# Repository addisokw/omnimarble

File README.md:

# OmniMarble -- Magnetic Coil Marble Coaster Digital Twin

A physics-accurate digital twin of a magnetic coil-launched marble roller coaster, built on NVIDIA's simulation stack (OpenUSD, PhysX, Kit SDK) with a Physics-Informed Neural Network (PINN) for real-time electromagnetic field computation.

## How It Works

A solenoid coil fires an RLC capacitor discharge through a coil to accelerate a ferromagnetic marble via electromagnetic force. The complete physics chain:

```
RLC Circuit (V, C, L, R)
    |
    v
Current I(t) -- underdamped oscillation with flyback diode
    |
    v
B-field (PINN: 6 inputs -> Br, Bz in single forward pass)
    |
    v
Gradient dB/dr, dB/dz (torch.autograd on PINN output)
    |
    v
Force F = (chi*V/mu0) * (B . nabla)B  -- with saturation + eddy braking
    |
    v
PhysX apply_force_at_pos() -- marble accelerates in Omniverse
```

### The PINN

The analytical Biot-Savart computation (30 loop iterations x scipy elliptic integrals) is replaced by a Physics-Informed Neural Network for real-time inference:

- **Architecture (v8, "physics by construction")**: NVIDIA PhysicsNeMo FullyConnected, 6x256 hidden, SiLU, skip connections. The network outputs a single scalar f; the vector potential is A_phi = r*f and the field is derived inside forward() via autograd: B_r = -r*df/dz, B_z = 2f + r*df/dr. This makes div(B)=0, curl consistency, and the on-axis boundary conditions **exact identities of the architecture**, not trained approximations.
- **Inputs**: (r, z, I, N, R_mean, L) -- spatial position + coil design parameters
- **Outputs**: (A_phi, B_r, B_z) -- same column contract as earlier direct-B models; the shared loader (`scripts/pinn_loader.py`) handles both generations via the checkpoint's `derived_b` flag
- **Key feature**: Model learns B/I (T/A), collapsing dynamic range across the full current range [0.5, 4000] A
- **Training**: 1.42M samples from analytical Biot-Savart (711 configs incl. failure-mined families), losses: data + far-field decay + z-mirror symmetry
- **Validation**: 5-level test suite -- field accuracy, gradient accuracy, force accuracy, design space coverage, physics consistency
- **Force**: needs field gradients, which are second derivatives of f (double backward through the forward-pass graph)

### RLC Circuit

The coil is driven by a capacitor discharge (underdamped RLC):

```
I(t) = (V0 / omega_d * L) * exp(-alpha * t) * sin(omega_d * t)
```

With coupled electromechanical ODE (back-EMF from marble motion), RK4 sub-stepping at 10us resolution, and flyback diode clamping.

Default circuit: 470uF capacitor, 50V charge, L=12.4uH, R_dc=0.080 ohm (config `resistance_ohm`) + 0.01 ESR + 0.02 wiring = R_total~=0.110 ohm -> underdamped (zeta=0.34). Peak current: 327A undamped amplitude V/(omega_d*L); ~198A true damped peak (the two pipelines historically reported different definitions -- see tests/test_coil_physics.py).

### Force Model

Force on a ferromagnetic sphere in a non-uniform field:

```
F = (chi_eff * V / mu0) * (B . nabla)B
```

Where:
- chi_eff = 3.0 (demagnetization-corrected susceptibility for a sphere)
- V = marble volume (mm^3)
- mu0 = 4*pi*1e-4 T*mm/A (mm-scaled)
- B and gradients from PINN autograd

Additional physics:
- **Saturation**: When B_internal > B_sat (1.8T), switches to saturated magnetization model
- **Eddy current braking**: F_eddy proportional to dB/dt and marble conductivity
- **Wire heating**: I^2*R thermal model with copper temperature coefficient

### Units

All computations use mm-based units:
- Distance: mm
- Current: A
- Field: T (Tesla)
- Force: mN (milliNewtons) -- because `[chi * mm^3 / (T*mm/A)] * T * T/mm = A*T*mm = mN`
- Mass: kg (PhysX requirement)
- mu0 = 4*pi*1e-4 T*mm/A

## Quick Start

### Prerequisites

- Python 3.12 or 3.13 — **not 3.14**, which has no `usd-core` wheels. If your
  system Python is newer, pin the project with `uv python pin 3.13` (uv
  downloads a managed interpreter; `.python-version` is gitignored).
- [uv](https://docs.astral.sh/uv/) package manager
- NVIDIA GPU (CUDA) for PINN training and inference
- [NVIDIA Kit SDK](https://github.com/NVIDIA-Omniverse/kit-app-template) for the Omniverse app

### 1. Install Dependencies

```bash
uv sync
```

This installs torch (CUDA 12.8), nvidia-physicsnemo, scipy, matplotlib, numpy, and other dependencies from `pyproject.toml`.

Verify the GPU is actually usable — a Blackwell card (RTX 50-series) needs
`sm_120` in torch's arch list, which the pinned cu128 build provides:

```bash
uv run python -c "import torch; print(torch.__version__, torch.cuda.get_arch_list())"
```

### 2. Train the PINN (or use existing checkpoint)

A trained checkpoint is included at `models/pinn_checkpoint/pinn_best.pt`
(v8 step-250k, `derived_b=True`). To retrain:

```bash
# Generate training data from analytical Biot-Savart (~1.42M samples)
uv run python scripts/generate_training_data.py

# Train v8 PINN (300k steps, ~4.7h on RTX 5090 — the data loss backprops
# through an autograd derivative, so every step is a double backward)
uv run python scripts/train_pinn.py
# Smoke test without touching the production checkpoint:
uv run python scripts/train_pinn.py --steps 500 --batch-size 16384 --out-name pinn_smoke
```

For remote GPU training (e.g., a more powerful machine on your network):
```bash
# Edit REMOTE_HOST and REMOTE_USER in the script, then:
bash scripts/remote_train.sh
# Pulls the result as pinn_v8_candidate.pt + step checkpoints to
# candidates/v8/ — promotion to pinn_best.pt is a manual decision after
# the adoption-gate evaluation (see below).
```

### 3. Validate the PINN

```bash
uv run python scripts/evaluate_pinn.py            # validates pinn_best.pt
uv run python scripts/evaluate_pinn.py --ckpt <path>   # validate a candidate
```

Runs a 5-level validation suite:
1. **Field accuracy**: Bz error vs analytical at 6 currents (12,800 points each)
2. **Gradient accuracy**: dB/dr, dB/dz via autograd vs finite-difference
3. **Force accuracy**: End-to-end F_z comparison at r=0 and r=5mm
4. **Design space**: 64 coil geometries (N x R_mean x L grid)
5. **Physics consistency**: div(B)=0, axial symmetry, z-mirror symmetry

Outputs:
- Console: PASS/FAIL per check
- Plots: `results/plots/pinn_validation/` (5 figures)
- JSON: `results/pinn_validation_report.json`
- Audit: `results/pinn_audit_report.md`

### 4. Analytical B-Field Validation

```bash
uv run python scripts/analytical_bfield.py
```

Generates reference plots in `results/plots/`.

### 5. Coil Design Optimizer

#### Web UI (Gradio)

```bash
uv run python scripts/coil_optimizer_app.py
```

Opens a browser UI for interactive multi-objective coil design optimization.
Features: constraint sliders, target-boost mode, Pareto plot, coupled ODE reranking.

#### CLI

```bash
uv run python scripts/optimize_coil_design.py
```

Headless optimization — prints top designs to console with Pareto plot saved to `results/`.

### 6. Run in NVIDIA Kit (Omniverse)

#### First-time setup

The Kit SDK is not vendored. `omnimarble.kit.bat` expects a
`kit-app-template` checkout **as a sibling of this repo**, with our app and
extension registered inside it. None of that wiring is tracked in git, so it
has to be redone on each new machine.

Verified against kit-app-template **110.2.0**. Windows needs no Visual Studio
— that template disables the C++ build step on `windows-x86_64`.

```cmd
REM 1. Clone kit-app-template next to this project
git clone https://github.com/NVIDIA-Omniverse/kit-app-template.git ..\kit-app-template

REM 2. A fresh clone has no source/ tree at all -- create it.
mkdir ..\kit-app-template\source\apps
mkdir ..\kit-app-template\source\extensions

REM 3. Register the app. Template 110.x expects a FLAT .kit file in
REM    source/apps -- not the nested apps/<name>/<name>.kit of older releases.
copy source\apps\omnimarble\omnimarble.kit ..\kit-app-template\source\apps\

REM 4. Link the extension back here so it stays live-editable. Path.resolve()
REM    follows the junction, so the extension's config/coil_params.json
REM    ancestor-walk still finds this project root.
mklink /J ..\kit-app-template\source\extensions\omni.marble.coaster ^
          source\extensions\omni.marble.coaster
```

Then register the app in the two build files in `../kit-app-template`.
Extensions are auto-discovered from the directory layout, so only the app
needs declaring:

```lua
-- premake5.lua -- append after the "Apps:" comment at the end
define_app("omnimarble.kit")
```

```toml
# repo.toml -- the section already exists with an empty list; fill it in
[repo_precache_exts]
apps = [
    "${root}/source/apps/omnimarble.kit",
]
```

Finally build (downloads ~10GB, one-time):

```cmd
cd ..\kit-app-template
.\repo.bat build
cd ..\omnimarble
```

#### Launch

```cmd
omnimarble.kit.bat
```

This launches Kit with the extension loaded directly from `source/extensions/` (live editing).

**First launch is slow.** The extension pip-installs its own torch into Kit's
embedded Python (3.12) at
`%LOCALAPPDATA%\ov\data\Kit\omnimarble\1.0\pip3-envs\default-3.12` — a
separate environment from this project's `.venv`. Both `torch` and
`torchvision` are pinned to `+cu128` builds in `extension.py`
(`TORCH_CUDA_VERSION` / `TORCHVISION_CUDA_VERSION`); without the pins pip
prefers PyPI's CPU-only Windows wheel and the PINN runs ~13x slower with no
other symptom. A healthy startup logs:

```
[PINN] torch 2.10.0+cu128 (CUDA 12.8), physicsnemo ready
[PINN] Loaded on cuda, checkpoint: ...\pinn_best.pt
```

If it says `CUDA None` or `Loaded on cpu`, a stale wheel is cached:
`omni.kit.pipapi.install` skips whenever the module already imports, so
delete `torch*` from that `pip3-envs` directory and relaunch. Note that
`torchvision` must go back too — `physicsnemo` imports `timm`, which imports
`torchvision`, and its absence surfaces misleadingly as *"Checkpoint was
trained with physicsnemo backend but nvidia-physicsnemo is not installed"*.

#### In the Kit app

1. Click **Load Scene** to open the USD marble coaster scene
2. Click **Configure PhysX** to set CCD, 500Hz timestep, damping
3. Click **Start Simulation** -- marble rolls down the track, triggers IR gates, fires the coil
4. Watch the console log for real-time telemetry (current, field, force, velocity)
5. Adjust **Charge Voltage** and **Capacitance** in the UI panel, click **Update Parameters**
6. Click **Stop Simulation** -- the run's trajectory is written to
   `results/trajectories/kit_launch_<V>V_<C>uF_<timestamp>.csv`

#### Scripted autorun (reproducible launch runs)

The full sequence (load scene, configure PhysX, voltage override, start,
stop after the exit gates fire, write CSV, quit) can be driven without
clicking:

```cmd
omnimarble.kit.bat --/exts/omni.marble.coaster/autorun=true --/exts/omni.marble.coaster/autorunVoltage=300
```

Optional: `autorunMaxSimSeconds` (default 12), `autorunKeepOpen=true` to
leave the app running after the CSV is written.

#### Trajectory export

Every physics step records time, position (world + coil-local z_along/r),
velocities, coil current, capacitor voltage, PINN force and Bz, wire
temperature, and trigger/cutoff flags. The CSV starts with `# key=value`
metadata lines (run parameters, PINN checkpoint + step, gate times,
approach/exit velocity, boost ratio).

A committed reference artifact from the real Kit/PhysX/PINN path:
`results/trajectories/kit_launch_300V_470uF_20260702_174018.csv` — 300V run,
approach 208 mm/s, gate-measured exit 937.5 mm/s (**4.5x boost**).

Use it to check a fresh machine: rerun the autorun command above and diff.
The gate-measured numbers and the `current_A` / `V_cap_V` / `Bz_T` /
`wire_temp_C` columns should match exactly. Positions and velocities drift
slightly (sub-0.1mm, well under 1% on velocity) — that is PhysX solver
nondeterminism across machines, not a broken setup.

#### What happens during simulation

1. Marble rolls down the starter slope under gravity
2. Two velocity-measurement IR gates compute approach velocity
3. Entry gate triggers the RLC discharge
4. Coupled electromechanical ODE computes current with 10us sub-stepping
5. PINN computes B-field, autograd computes gradients, force is applied via PhysX
6. Cutoff gate (MOSFET switch) kills the pulse when marble passes coil center
7. Two exit gates measure the launch velocity and compute boost ratio

## Project Structure

```
config/
  coil_params.json              # Source of truth: coil geometry + RLC circuit params

scripts/
  analytical_bfield.py          # Biot-Savart B-field (elliptic integrals) -- ground truth
  generate_training_data.py     # PINN training data from analytical solution (1.42M samples)
  pinn_loader.py                # Shared checkpoint loader + inference (legacy & derived-B)
  train_pinn.py                 # v8 derived-B PINN training (PhysicsNeMo)
  evaluate_pinn.py              # 5-level PINN validation suite (--ckpt for candidates)
  evaluate_candidates.py        # Multi-checkpoint Pareto comparison
  v7_optimization_diagnostic.py # PINN ranking stability diagnostic (--ckpt)
  physical_accuracy_audit.py    # Physics consistency validation
  validate_physics.py           # Physics validation utilities
  validate_kit_simulation.py    # Headless mirror of Kit physics (--field pinn|analytical)
  coil_optimizer_core.py        # Shared optimization engine (screening + coupled reranking)
  coil_optimizer_app.py         # Gradio web UI for coil design optimizer
  optimize_coil_design.py       # CLI coil design optimizer
  warp_bfield_solver.py         # PINN-based solver for headless simulation
  rlc_circuit.py                # RLC circuit utilities (saturation, eddy braking)
  remote_train.sh               # Remote GPU training via SSH
  generate_coil.py              # Parametric coil mesh generation
  em_force_injection.py         # Standalone EM force simulation
  simulation_loop.py            # Full orchestration loop
  optimize_launch.py            # Differentiable parameter optimization
  create_marble.py              # Marble actor creation
  compose_scene.py              # Scene composition from USD layers
  convert_stl_to_usd.py         # STL → USD conversion
  add_visuals.py                # Visual enhancement
  setup_launch_scene.py         # Launch scene setup
  run_physics_test.py           # Physics test runner

source/                         # NVIDIA Kit extension
  apps/omnimarble/
    omnimarble.kit              # Kit app configuration
  extensions/omni.marble.coaster/
    config/extension.toml       # Extension settings (overridable defaults)
    omni/marble/coaster/
      extension.py              # Main extension: RLC + PINN + PhysX force + UI + autorun
      coil_physics.py           # Pure-Python coil/RLC physics (unit-testable, no Kit deps)

tests/                          # pytest suite (uv run pytest)
  test_coil_physics.py          # Derived values vs config, RLC, gates, cross-checks
  test_rlc_circuit.py           # Saturation/eddy/thermal helpers, mm/mN/T unit system
  test_pinn_loader.py           # Loader version detection, derived-B structural guarantees

models/
  pinn_checkpoint/
    pinn_best.pt                # Production checkpoint: v8 step-250k, derived_b=True
                                # (historical v3-v7 checkpoints live in git history;
                                #  candidates/ holds gitignored periodic checkpoints)

usd/                            # USD scene layers
  marble_coaster_scene.usda     # Composed scene (references all layers)
  marble_actor.usda             # Marble rigid body (mass=0.00408kg)
  coil_geometry.usda            # Coil mesh
  coil_properties.usda          # Coil electrical properties
  track_geometry.usda           # Track collision mesh
  marble_trajectory.usda        # Trajectory reference
  physics_config.usda           # PhysX configuration
  visual_config.usda            # Visual settings

results/
  pinn_validation_report.json   # Validation metrics (machine-readable)
  pinn_audit_report.md          # Full PINN audit trail
  plots/                        # Generated validation plots

omnimarble.kit.bat              # Launch Kit from project root
```

## Configuration

All physical parameters live in `config/coil_params.json`:

```json
{
  "inner_radius_mm": 12.0,
  "outer_radius_mm": 18.0,
  "length_mm": 30.0,
  "num_turns": 30,
  "capacitance_uF": 470.0,
  "charge_voltage_V": 50.0,
  "esr_ohm": 0.01,
  "wiring_resistance_ohm": 0.02,
  "has_flyback_diode": true,
  "switch_type": "MOSFET"
}
```

The Kit extension reads this JSON as the primary source of truth. UI fields in Kit override individual values at runtime.

**Physical-build note:** the persisted `inductance_uH`/`resistance_ohm`
derive from a 12mm-former winding assumption, while the field model (and
the PINN trained on it) places the windings at R_mean = 15mm — no single
physical coil satisfies both. Build real coils to the field geometry and
overwrite these two values with LCR-measured ones; see
`hardware/README.md` ("Supported coils" / build sheet) for the full
analysis.

### Getting a stronger launch

The default 50V/470uF circuit stores only 0.59J — at 50V the EM force barely
changes the trajectory versus a plain gravity roll. For a visible launch:
- **300V / 470uF**: 21J stored — **demonstrated in Kit: 4.5x gate-measured
  boost** (artifact: `results/trajectories/kit_launch_300V_470uF_20260702_174018.csv`)
- To improve efficiency, increase coil inductance (more turns, tighter winding) so the discharge period (~5-20ms) matches the marble's transit time through the coil

## PINN Training Details

### Architecture (v8, physics by construction)
- NVIDIA PhysicsNeMo FullyConnected backbone
- 6 inputs: (r, z, I, N, R_mean, L); 1 raw output: scalar f
- A_phi = r*f; B_r = -r*df/dz and B_z = 2f + r*df/dr derived via autograd
  in forward() — div(B)=0, curl consistency, and on-axis BCs are exact
- 6 hidden layers x 256 units, SiLU activation, skip connections
- B/I normalization: model learns B/I (T/A), caller multiplies by I
- Canonical model + loader: `scripts/pinn_loader.py` (`BFieldPINNDerived`)

### Training data
- 1.42M samples from analytical Biot-Savart
- 75k spatial point pool: 30k dense near coil + 20k boundary-enriched + 5k on-axis + 20k far-field
- 711 parameter configs: grid corners + random + failure-mined N=10/R=8 families
- Per-config: 1500 general + 500 config-adaptive boundary points

### Loss function (v8)
- **Data loss**: MSE on derived B_r/I and B_z/I (backprops through the
  autograd derivative — the dominant per-step cost)
- **Far-field decay** (weight 0.1): fields -> 0 far from coil
- **z-mirror symmetry** (weight 0.5): Bz even, Br odd in z
- Progressive ramp: physics weights scale from 0.1x to 1.0x over first 20k steps
- Removed vs v7 (now exact by construction): curl, divergence-free, on-axis
  boundary conditions; gradient supervision dropped (third-order, marginal)
- Checkpoint selection by data loss + periodic saves for a post-hoc sweep

### Current validation status (v8 step-250k, production — 2026-07-02)

| Level | Check | Result |
|-------|-------|--------|
| 1 | Field accuracy (mean/max Bz error) | FAIL max-only (mean 0.86%, max 27.8% at winding singularities; informational) |
| 2 | Gradient accuracy (dBz/dz mean + P99) | PASS (P99 3.05%) |
| 3 | Force accuracy (peak err, correlation, zero-crossing) | PASS (2.7% / 3.0%, r>0.994) |
| 4 | Design space (64 configs under 5%) | PASS (95.3%, worst 7.75%) |
| 5 | Physics consistency (div=0, symmetry) | PASS (div(B)=0 exact by construction) |

Optimizer-ranking diagnostic vs analytical reference: Spearman r=1.000,
Kendall tau=0.992 over 60 candidates — safe for design optimization.

See `results/pinn_audit_report.md` for the full audit trail including all
training iterations (v1-v8) and the adoption-gate decision.

## License

MIT

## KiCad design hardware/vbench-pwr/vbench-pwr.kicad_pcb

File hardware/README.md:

# OmniMarble driver board (60V-class SELV coilgun pulse driver)

Experimental-side electronics for the OmniMarble digital twin: drives a
real coil with the same fire/cutoff logic as the simulation's Kit
extension and emits telemetry in the sim's trajectory-CSV format for
direct sim-to-real comparison.

> ⚠️ **vNext — on hold (2026-07-06).** This integrated driver board is not the
> current path. The launch concept is still unproven, so we stepped back to a
> bench rig built from off-the-shelf modules — see **[`V0_BENCH_RIG.md`](V0_BENCH_RIG.md)**.
> This board is DRC-clean and preserved; revisit once V0 proves the concept out.

**Status: layout final — fully routed, electrically DRC-clean (0 unconnected /
shorts / clearance / parity), all validators green, and the JLCPCB fab/assembly
package generated (`hardware/fab/jlc/`). Externally reviewed.**

- Operating point: bank charged **24.5–55 V** (63 V-rated capacitors,
  hardware OVP trips 59.1–62.0 V worst-case, asserted in
  `scripts/calcs.py`), one shot per several seconds.
- Bank: 5× snap-in positions, 2200 µF/63 V each (baseline 2 populated =
  4400 µF; max 11000 µF).
- Switch: 3× paralleled 150 V TOLL MOSFETs, designed to a **600 A / 2 ms**
  pulse point; MOSFET-cutoff + freewheel topology reproduces the sim's
  circuit model.
- All engineering numbers in `design-calcs.md` are generated and
  margin-asserted by `scripts/calcs.py` — do not hand-edit.

## Supported coils

The coil is off-board (J5 barrier terminals) and interchangeable. A coil
is **validated** iff it satisfies the envelope swept by `calcs.py` at the
worst configuration (11000 µF bank at 55 V):

> **L ≥ 1 µH AND R_total ≥ 90 mΩ** (total series resistance *including*
> leads and lugs — keep leads short and heavy)

Below the envelope the pulse can exceed the 600 A switch design point —
do not fire. The envelope numbers live in `coil-envelope.json` (generated
by calcs.py) and are printed on the flyback schematic sheet next to J5;
the full safe/unsafe sweep table is in `design-calcs.md`.

### Validated default: demo coil (the coil the simulation models)

| Parameter | Value |
|---|---|
| Turns / wire | 30 × 0.8 mm (AWG20), single layer |
| Geometry | inner r 12 mm, outer r 18 mm, length 30 mm |
| Inductance | 12.406 µH |
| R_dc / R_total | 80.2 mΩ / **110.2 mΩ** (incl. 30 mΩ ESR+wiring budget) |
| At 55 V / 11000 µF | ~420 A peak, ~1.1 ms, 16.6 J |

Using this coil keeps hardware runs directly comparable to Kit runs
(`config/coil_params.json` is the shared source of truth).

### KNOWN MODEL INCONSISTENCY (affects how you build the coil)

The simulation is internally inconsistent about where the windings sit:

- The **field model** (`analytical_bfield.solenoid_field`, which the PINN
  was trained on and the launch force derives from) places all 30 turns
  at a **single 15.0 mm radius** — the mean of config's inner 12 / outer
  18 mm.
- The **circuit model** (Wheeler inductance + winding resistance in
  `coil_physics.py` / `rlc_circuit.py`) assumes a single layer of 0.8 mm
  wire on a 12 mm former (wire centers ~12.4 mm), which is where config's
  persisted `inductance_uH = 12.406` and `resistance_ohm = 0.0802` come
  from.

No physical coil satisfies both. **Resolution: build to the FIELD
geometry** (that is what the PINN/force model is being validated
against), then reconcile the circuit side by measurement — the config
accepts measured `inductance_uH` / `resistance_ohm` and the RLC model
uses whatever is there. Building at 12 mm instead would bias the field
test: closer windings give a measurably stronger on-axis field than the
model predicts.

### Coil build sheet — experiment #1 (demo coil, field-geometry build)

The field model uses **ideal loop centers**: 30 loops at radius 15.0 mm
with centers at `np.linspace(-15, +15, 30)`. The physical winding must
match **turn centers**, not wire edges. Machine-readable spec:
`hardware/scripts/parts.py DEMO_COIL_BUILD`, contract-tested against the
field model by `tests/test_coil_physics.py::
test_demo_coil_build_matches_field_model` (fails if either side drifts).

| Item | Spec |
|---|---|
| Target geometry | **Wire CENTER radius = 15.0 mm** (this is the spec; former OD follows from your wire) |
| Former | For 0.87 mm finished wire OD (0.8 mm copper + 2×0.035 mm enamel): **~29.13 mm OD**. Measure your wire's finished OD and set former OD = 2×(15.0 − OD/2). 32 mm winding window between flanges |
| Wire | 0.8 mm copper (AWG20) enameled magnet wire, ~3 m incl. leads |
| Turns | **30 turns, single layer, one direction** |
| Spacing | **30 turn CENTERS evenly spanning 30.0 mm** → center-to-center pitch **30/29 ≈ 1.034 mm** (not 1.000). First and last turn centers sit at ±15.0 mm from coil center. NOT close-wound (that compresses the span to ~26 mm and shifts the field profile) |
| Leads | Short and heavy (>=AWG16 or doubled), crimped ring lugs to J5 |

Winding tips: score/print **1.034 mm-pitch** guide grooves (or a printed
thread) so the groove *centers* span exactly 30.0 mm; secure the ends
(CA glue) before the winding relaxes; leave 100 mm tails.

**Verify after winding** (LCR meter ~1 kHz + milliohm measurement), then
**write the measured values into `config/coil_params.json`** so sim and
hardware run identical circuit numbers:

| Quantity | Expected (field-geometry build) | Config's current value |
|---|---|---|
| Inductance | **~17.3 uH** (Wheeler at 15 mm) | 12.406 uH (12.4 mm assumption) |
| R_dc | **~97 mOhm** (2.83 m of AWG20) | 80.2 mOhm |
| R_total w/ leads | ~125–130 mOhm | 110.2 mOhm |
| Envelope check | 127 mOhm >= 90 mOhm, 17 uH >= 1 uH — inside; worst-case pulse ~430 A vs the 600 A design point | — |

### Experiment #2 (after #1 validates the model)

Wind the optimizer-recommended coil below; its predicted **+1.0 m/s
boost is itself a falsifiable prediction** of the digital twin.

### Optimizer-recommended coil for THIS board (55 V / 600 A constrained)

`uv run python scripts/optimize_coil_design.py --max-voltage 55 --max-current 600`
(PINN + coupled-ODE screening, 2000 LHS candidates, run 2026-07-03):

| Parameter | Value |
|---|---|
| Turns / wire | **75 × AWG18 (1.024 mm), 3 layers** |
| Geometry | inner r 8.5 mm, outer r 11.8 mm, length 30.5 mm |
| Inductance / R | 49.4 µH / R_dc 99 mΩ → R_total ~129 mΩ |
| Drive point | ~51 V, ~3700 µF (2 bank cans ≈ 4400 µF is the closest fit) |
| Pulse | 228 A peak, 1.6 ms, 4.8 J, ΔT ≈ 0.3 °C |
| Predicted boost | **+1.0 m/s (0.5 → 1.5 m/s, ~3×)** |

Envelope check: 129 mΩ ≥ 90 mΩ and 49.4 µH ≥ 1 µH — inside. Note the
earlier optimizer result quoted in the repo (396 V / 247 J design) was
computed for an unconstrained rig and is **not** a recommendation for
this board.

Caveat: these predictions come from the PINN + analytical circuit model.
Validating them against reality is this board's entire purpose — treat
the boost figure as a hypothesis, not a spec.

## Safety summary (details in design-calcs.md)

- Hardware interlock: FIRE = MCU_FIRE AND ARM-keyswitch (74LVC1G08), and
  the gate drivers are only powered through the E-STOP (NC) + keyswitch
  loop. Explicit pulldowns on all fire nets.
- Boost charging is fail-safe inhibited: a dead/absent Pico cannot charge.
- Hardware OVP (CJ431 ±0.5 %) independent of the MCU.
- Permanent 6.8 k bleed (3τ ≈ 224 s) + commanded 200 Ω dump (<5 V in
  5.3 s) + hardwired live-bank LED.
- Relays never break DC under load (sequencing: precharge before close,
  boost-inhibit before open, dump closes onto 0.28 A).

## Order/production gates

- `uv run python hardware/scripts/validate.py` — schematic completeness
  (review mode; warns on ORDER-REVIEW placeholders).
- `uv run python hardware/scripts/validate.py --production` — fab-export
  gate; **fails** while any ORDER-REVIEW placeholder remains. Currently
  clean: the R24 bank-bleed resistor is resolved to UNI-ROYAL
  25121WJ0682T4E / LCSC **C26073** (6.8 k, 1 W, 2512).
- BOMs: `bom/bom.csv` (engineering), `bom/bom_rail_emit.csv` /
  `bom_rail_recv.csv` (gate-rail variants incl. common parts). JLC
  assembly exports (`fab/jlc/bom_jlc.csv`, `cpl_jlc.csv`) are generated by
  `gen_fab.py`.

## Status & next phases

- **Done:** schematic; 4-layer 2 oz PCB layout (routed, electrically
  DRC-clean, datasheet-verified footprints for TOLL-8 / 9.5 mm barrier /
  5930 shunt / HF3FF relay); and the JLCPCB fab/assembly package
  (`hardware/fab/jlc/`, via `gen_fab.py`).
- **Next:** upload to JLC and clear its DFM (see `fab/jlc/ORDER_NOTES.md`);
  Pico firmware (fire/cutoff state machine, gate timestamps, DMA current
  capture, TRAJ_COLUMNS-compatible telemetry) + `compare_sim_real.py`;
  bring-up procedure — first power at 25 V floor, staged to 55 V, and
  **verify OVP trip + boost regulation before installing max bank
  capacitance or firing into the coil** (the 63 V-cap / 59.1–62.0 V OVP
  window is tight).

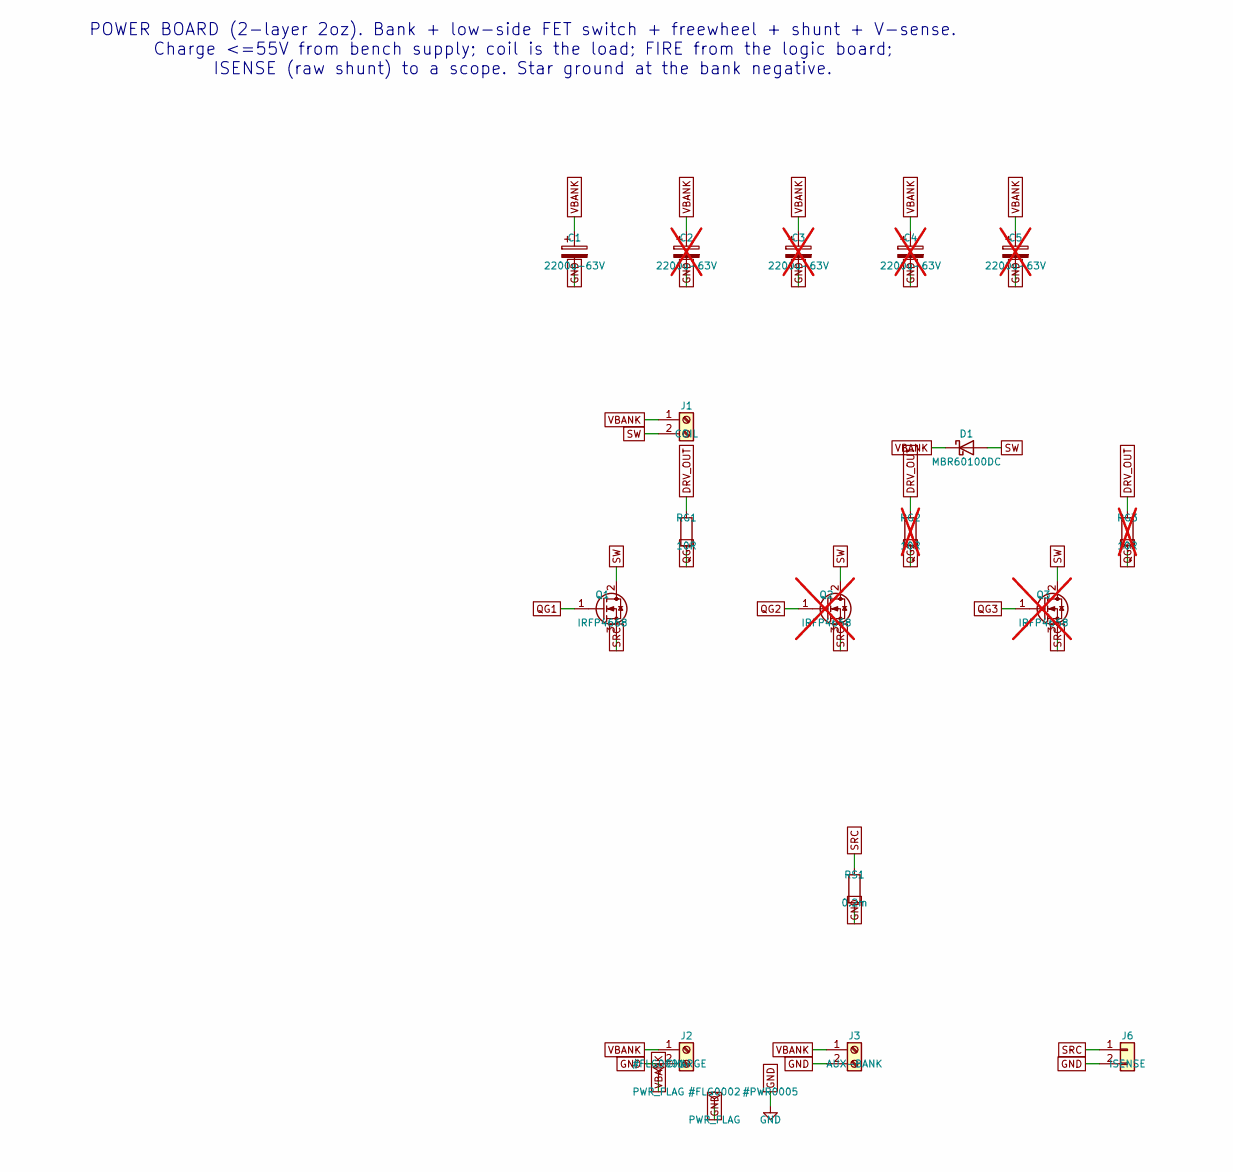
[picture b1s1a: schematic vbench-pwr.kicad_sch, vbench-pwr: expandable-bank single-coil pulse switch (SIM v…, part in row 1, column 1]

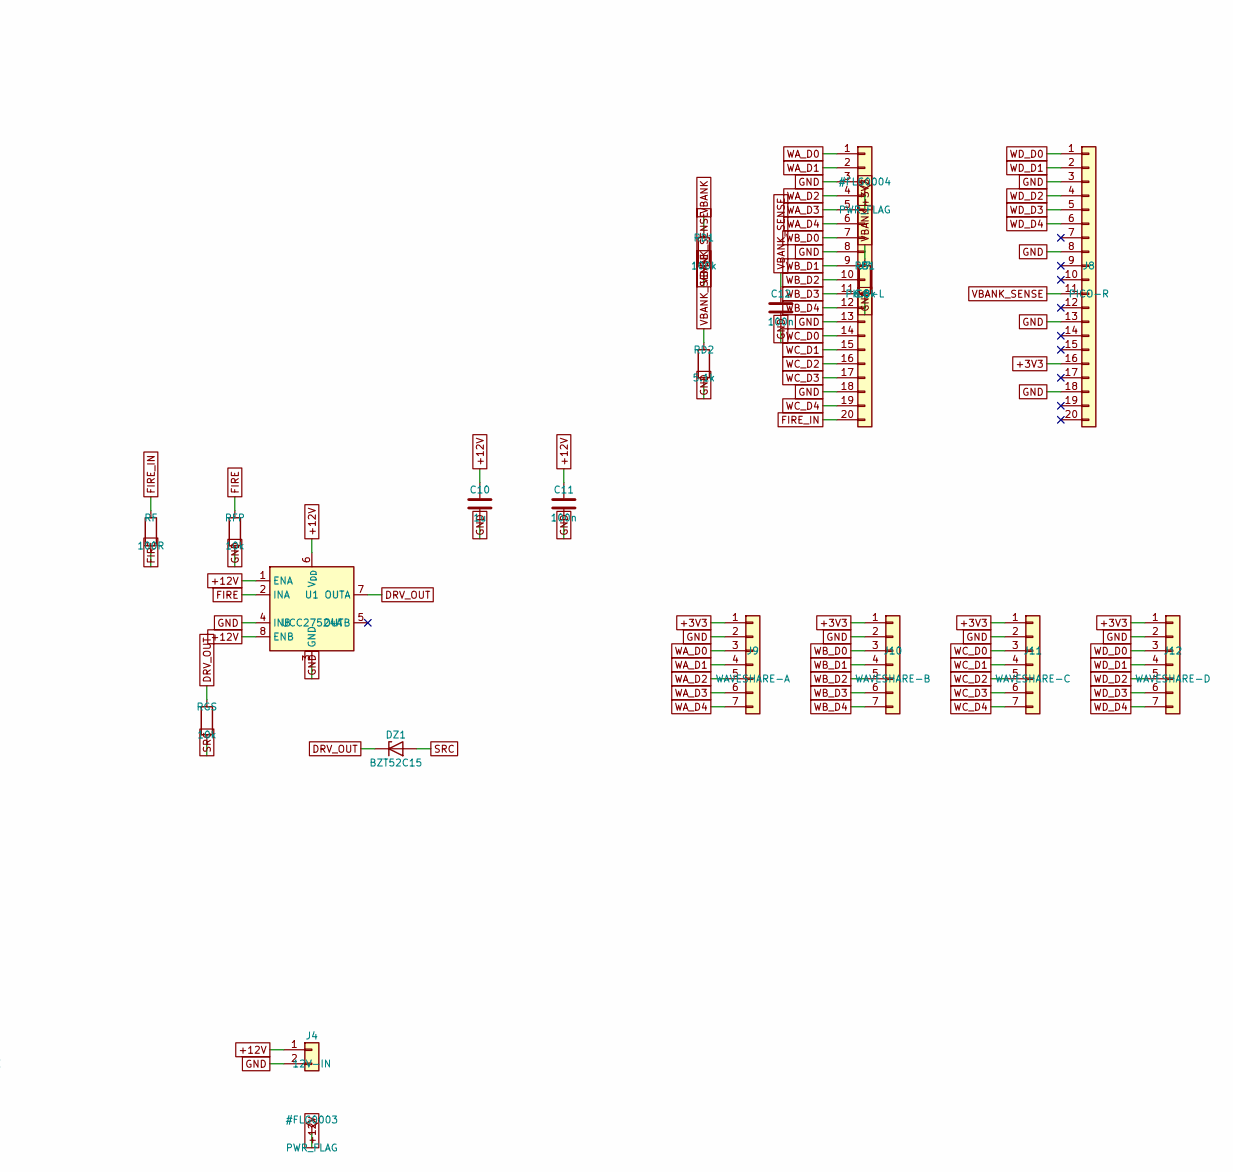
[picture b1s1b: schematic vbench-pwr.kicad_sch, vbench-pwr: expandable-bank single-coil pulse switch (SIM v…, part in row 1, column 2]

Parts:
C1: 2200u-63V; CP_Radial_D18.0mm_P7.50mm; LCSC C47858
C2, C3, C4, C5: 2200u-63V; CP_Radial_D18.0mm_P7.50mm; LCSC C47858; not fitted
C10: 1u; C_0805_2012Metric
C11, C12: 100n; C_0805_2012Metric
D1: MBR60100DC; D2PAK_MBR60100DC; LCSC C6069541
DZ1: BZT52C15; D_SOD-123; LCSC C19077412
J1: COIL; TerminalBarrier_1x02_P9.50mm; LCSC C707836
J2: CHARGE; TerminalBarrier_1x02_P9.50mm; LCSC C707836
J3: AUX-BANK; TerminalBarrier_1x02_P9.50mm; LCSC C707836
J4: 12V-IN; PinHeader_1x02_P2.54mm_Vertical
J6: ISENSE; PinHeader_1x02_P2.54mm_Vertical
J7: PICO-L; PinSocket_1x20_P2.54mm_Vertical; LCSC C50984
J8: PICO-R; PinSocket_1x20_P2.54mm_Vertical; LCSC C50984
J9: WAVESHARE-A; PinHeader_1x07_P2.54mm_Vertical
J10: WAVESHARE-B; PinHeader_1x07_P2.54mm_Vertical
J11: WAVESHARE-C; PinHeader_1x07_P2.54mm_Vertical
J12: WAVESHARE-D; PinHeader_1x07_P2.54mm_Vertical
Q1: IRFP4668; TO-247-3_Vertical
Q2, Q3: IRFP4668; TO-247-3_Vertical; not fitted
RB1: 6.8k; R_2512_6332Metric; LCSC C26073
RD1: 100k; R_0805_2012Metric; LCSC C25803
RD2: 5.1k; R_0805_2012Metric; LCSC C23186
RF: 100R; R_0805_2012Metric
RFP: 10k; R_0805_2012Metric; LCSC C25804
RG1: 10R; R_0805_2012Metric; LCSC C22859
RG2, RG3: 10R; R_0805_2012Metric; LCSC C22859; not fitted
RGS: 10k; R_0805_2012Metric; LCSC C25804
RS1: 0.2m; Shunt_5930; LCSC C469442
U1: UCC27524A; SOIC-8_3.9x4.9mm_P1.27mm; LCSC C185857

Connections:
+3V3: J8.16, J9.1, J10.1, J11.1, J12.1
+12V: C10.1, C11.1, J4.1, U1.1 (ENA), U1.6 (V_{DD}), U1.8 (ENB)
DRV_OUT: DZ1.1 (K), RG1.1, RG2.1, RG3.1, RGS.1, U1.7 (OUTA)
FIRE: RF.2, RFP.1, U1.2 (INA)
FIRE_IN: J7.20, RF.1
GND: C1.2, C2.2, C3.2, C4.2, C5.2, C10.2, C11.2, C12.2, J2.2, J3.2, J4.2, J6.2, J7.3, J7.8, J7.13, J7.18, J8.3, J8.8, J8.13, J8.18, J9.2, J10.2, J11.2, J12.2, RB1.2, RD2.2, RFP.2, RS1.2, U1.3 (GND), U1.4 (INB)
QG1: Q1.1 (G), RG1.2
QG2: Q2.1 (G), RG2.2
QG3: Q3.1 (G), RG3.2
SRC: DZ1.2 (A), J6.1, Q1.3 (S), Q2.3 (S), Q3.3 (S), RGS.2, RS1.1
SW: D1.2 (A), J1.2, Q1.2 (D), Q2.2 (D), Q3.2 (D)
VBANK: C1.1, C2.1, C3.1, C4.1, C5.1, D1.1 (K), J1.1, J2.1, J3.1, RB1.1, RD1.1
VBANK_SENSE: C12.1, J8.11, RD1.2, RD2.1
WA_D0: J7.1, J9.3
WA_D1: J7.2, J9.4
WA_D2: J7.4, J9.5
WA_D3: J7.5, J9.6
WA_D4: J7.6, J9.7
WB_D0: J7.7, J10.3
WB_D1: J7.9, J10.4
WB_D2: J7.10, J10.5
WB_D3: J7.11, J10.6
WB_D4: J7.12, J10.7
WC_D0: J7.14, J11.3
WC_D1: J7.15, J11.4
WC_D2: J7.16, J11.5
WC_D3: J7.17, J11.6
WC_D4: J7.19, J11.7
WD_D0: J8.1, J12.3
WD_D1: J8.2, J12.4
WD_D2: J8.4, J12.5
WD_D3: J8.5, J12.6
WD_D4: J8.6, J12.7

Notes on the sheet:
POWER BOARD (2-layer 2oz). Bank + low-side FET switch + freewheel + shunt + V-sense. Charge <=55V from bench supply; coil is the load; FIRE from the logic board; ISENSE (raw shunt) to a scope. Star ground at the bank negative.

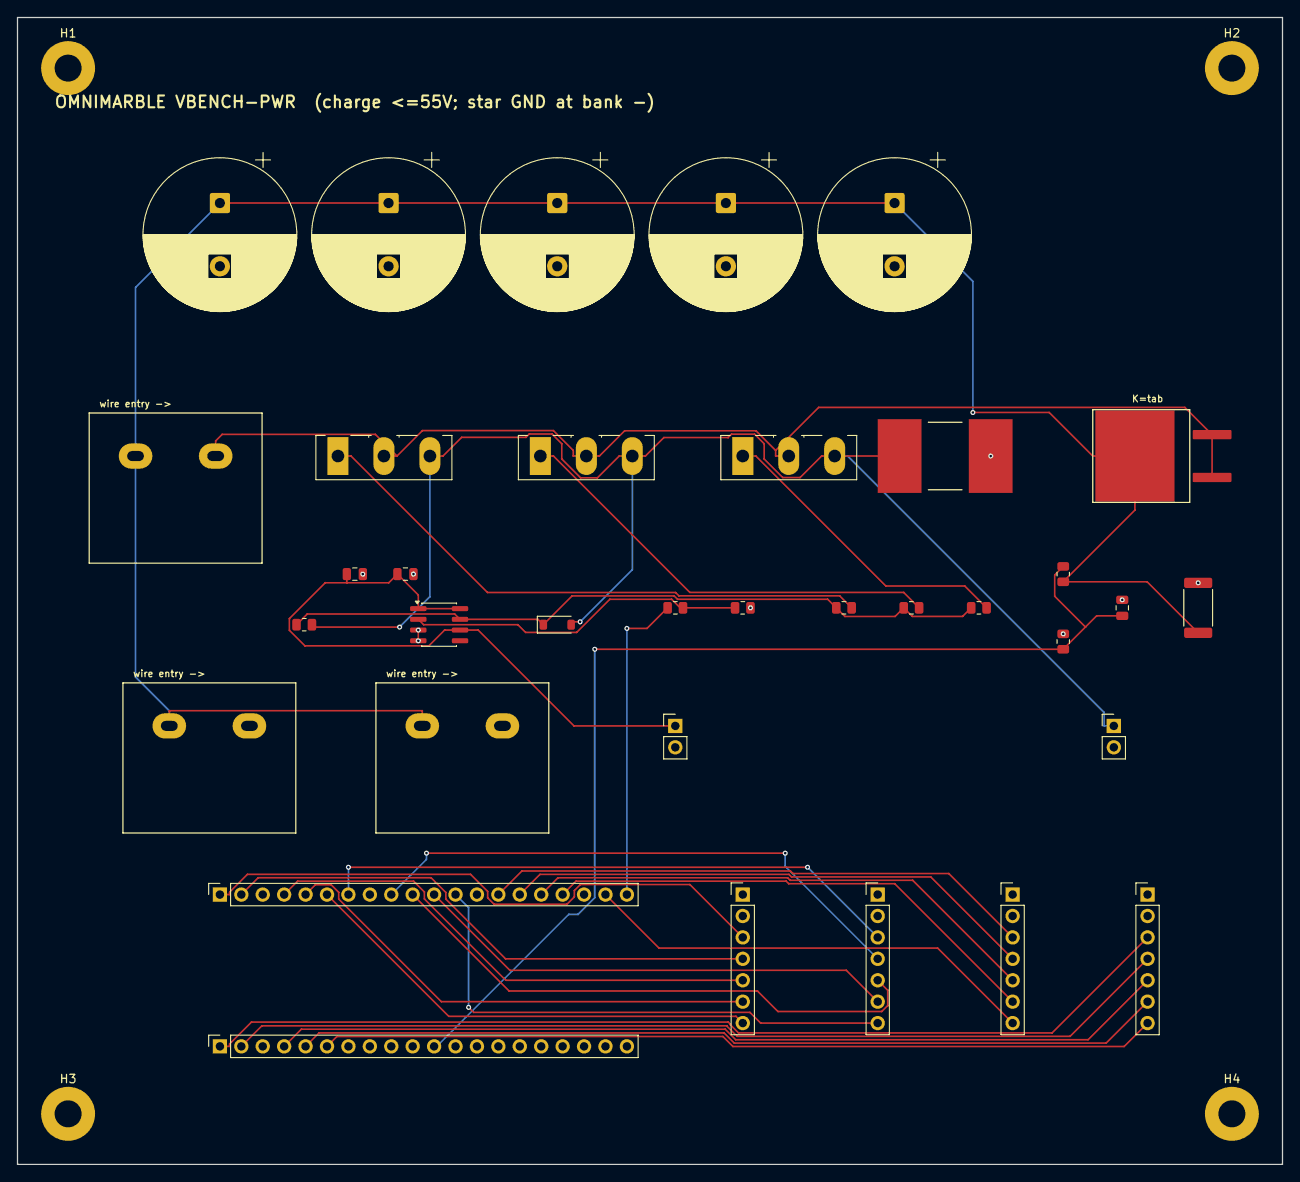
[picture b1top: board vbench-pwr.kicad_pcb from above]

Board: 4 copper layers, 150.0 x 136.0 mm, 39 parts (0 on the bottom side), 33 nets.

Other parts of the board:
H1, H2, H3, H4: MountingHole_3.2mm_M3_Pad

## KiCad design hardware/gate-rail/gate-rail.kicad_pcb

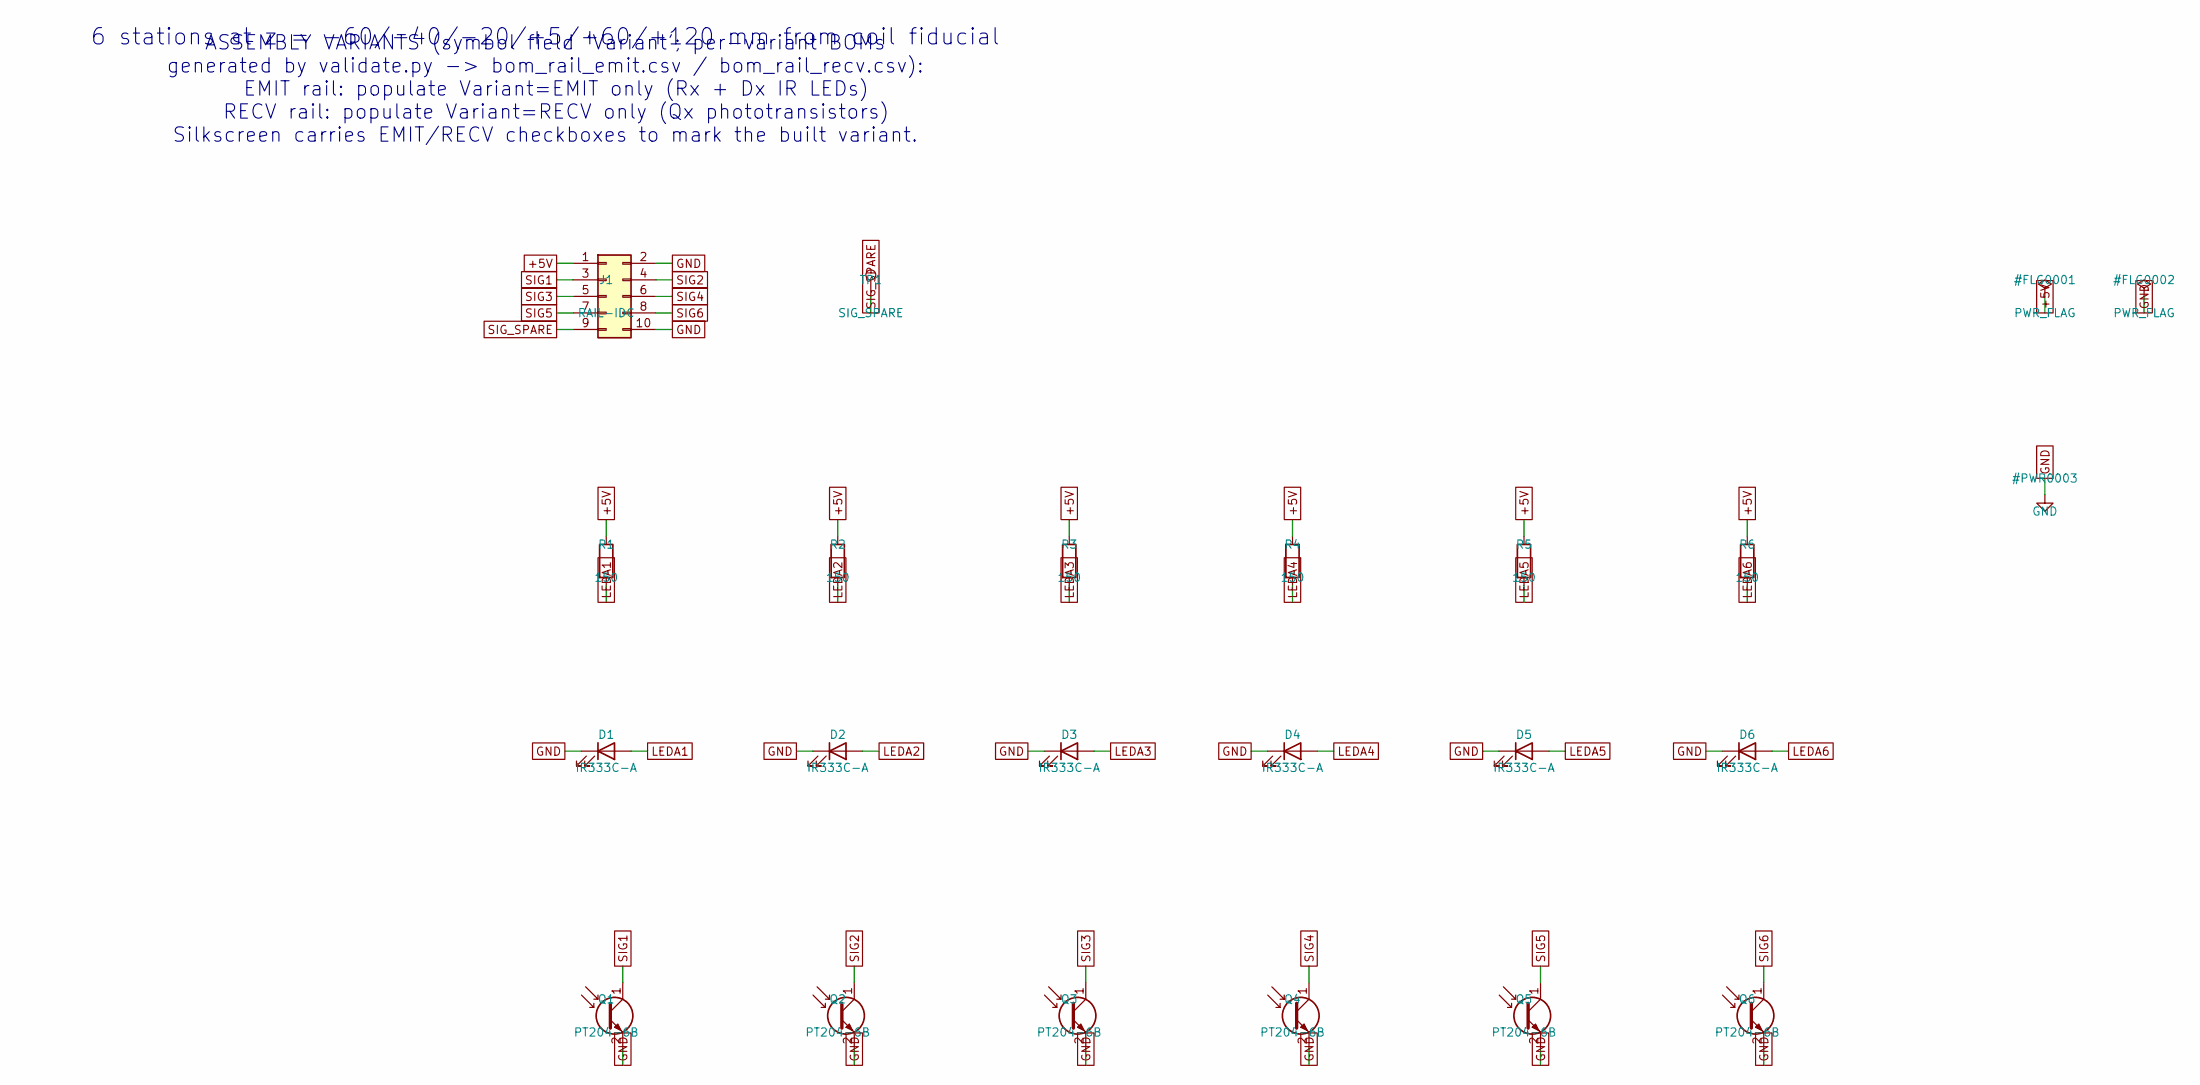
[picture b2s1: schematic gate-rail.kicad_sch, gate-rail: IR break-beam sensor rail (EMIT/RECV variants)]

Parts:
D1, D2, D3, D4, D5, D6: IR333C-A; LED_D5.0mm; LCSC C5130
J1: RAIL-IDC; IDC-Header_2x05_P2.54mm_Vertical; LCSC C5665
Q1, Q2, Q3, Q4, Q5, Q6: PT204-6B; LED_D3.0mm; LCSC C5133
R1, R2, R3, R4, R5, R6: 150; R_0603_1608Metric; LCSC C22808
TP1: SIG_SPARE; TestPoint_Pad_1.5x1.5mm

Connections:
+5V: J1.1, R1.1, R2.1, R3.1, R4.1, R5.1, R6.1
GND: D1.1 (K), D2.1 (K), D3.1 (K), D4.1 (K), D5.1 (K), D6.1 (K), J1.2, J1.10, Q1.2 (E), Q2.2 (E), Q3.2 (E), Q4.2 (E), Q5.2 (E), Q6.2 (E)
LEDA1: D1.2 (A), R1.2
LEDA2: D2.2 (A), R2.2
LEDA3: D3.2 (A), R3.2
LEDA4: D4.2 (A), R4.2
LEDA5: D5.2 (A), R5.2
LEDA6: D6.2 (A), R6.2
SIG1: J1.3, Q1.1 (C)
SIG2: J1.4, Q2.1 (C)
SIG3: J1.5, Q3.1 (C)
SIG4: J1.6, Q4.1 (C)
SIG5: J1.7, Q5.1 (C)
SIG6: J1.8, Q6.1 (C)
SIG_SPARE: J1.9, TP1.1

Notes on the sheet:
6 stations at z = -60/-40/-20/+5/+60/+120 mm from coil fiducial
ASSEMBLY VARIANTS (symbol field 'Variant'; per-variant BOMs generated by validate.py -> bom_rail_emit.csv / bom_rail_recv.csv): EMIT rail: populate Variant=EMIT only (Rx + Dx IR LEDs) RECV rail: populate Variant=RECV only (Qx phototransistors) Silkscreen carries EMIT/RECV checkboxes to mark the bui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

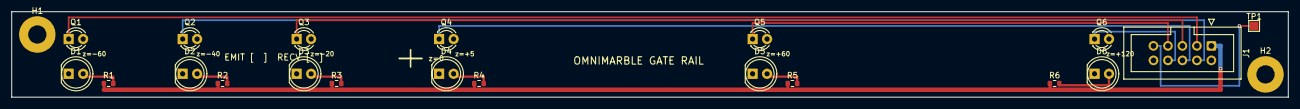
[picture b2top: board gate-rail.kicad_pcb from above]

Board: 2 copper layers, 224.0 x 15.0 mm, 22 parts (0 on the bottom side), 15 nets.

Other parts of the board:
H1, H2: MountingHole_3.2mm_M3_Pad

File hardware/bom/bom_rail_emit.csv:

Reference,Value,Footprint,LCSC
D1,IR333C-A,LED_THT:LED_D5.0mm,C5130
D2,IR333C-A,LED_THT:LED_D5.0mm,C5130
D3,IR333C-A,LED_THT:LED_D5.0mm,C5130
D4,IR333C-A,LED_THT:LED_D5.0mm,C5130
D5,IR333C-A,LED_THT:LED_D5.0mm,C5130
D6,IR333C-A,LED_THT:LED_D5.0mm,C5130
J1,RAIL-IDC,Connector_IDC:IDC-Header_2x05_P2.54mm_Vertical,C5665
R1,150,Resistor_SMD:R_0603_1608Metric,C22808
R2,150,Resistor_SMD:R_0603_1608Metric,C22808
R3,150,Resistor_SMD:R_0603_1608Metric,C22808
R4,150,Resistor_SMD:R_0603_1608Metric,C22808
R5,150,Resistor_SMD:R_0603_1608Metric,C22808
R6,150,Resistor_SMD:R_0603_1608Metric,C22808

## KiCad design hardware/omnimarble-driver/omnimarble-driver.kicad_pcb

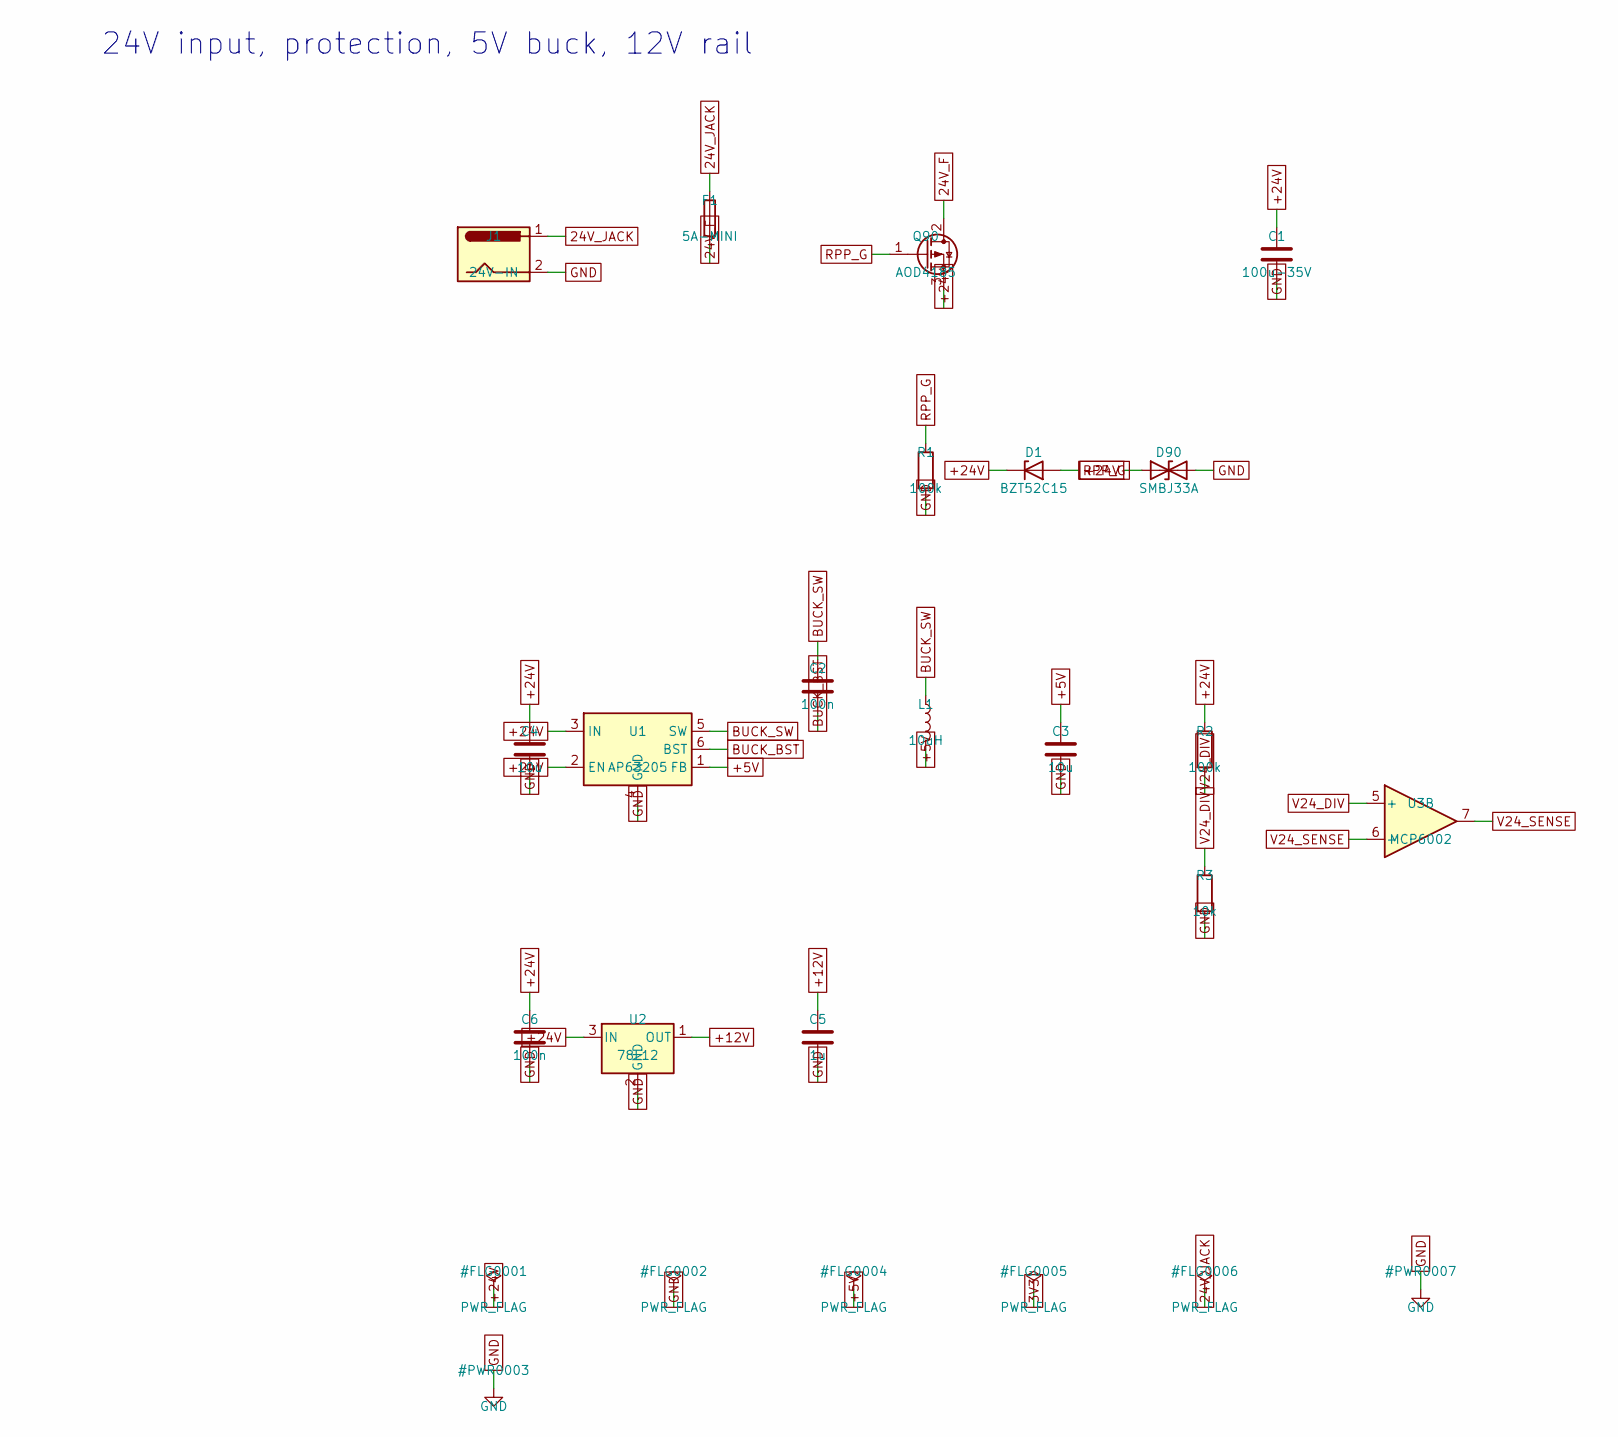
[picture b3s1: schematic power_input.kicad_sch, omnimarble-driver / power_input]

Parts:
C1: 100u-35V; CP_Elec_6.3x7.7; LCSC C176666
C2, C6: 100n; C_0603_1608Metric; LCSC C14663
C3, C4: 10u; C_0805_2012Metric; LCSC C15850
C5: 1u; C_0603_1608Metric; LCSC C15849
D1: BZT52C15; D_SOD-123; LCSC C19077412
D90: SMBJ33A; D_SMB; LCSC C19077586
F1: 5A-MINI; Fuseholder_Blade_Mini_Keystone_3568; LCSC C5249699
J1: 24V-IN; BarrelJack_Horizontal; LCSC C381116
L1: 10uH; L_Changjiang_FNR6045S; LCSC C79272
Q90: AOD4185; TO-252-2; LCSC C77317
R1, R2: 100k; R_0603_1608Metric; LCSC C25803
R3: 10k; R_0603_1608Metric; LCSC C25804
U1: AP63205; TSOT-23-6; LCSC C2071056
U2: 78L12; SOT-89-3; LCSC C347272
U3: MCP6002; SOIC-8_3.9x4.9mm_P1.27mm; LCSC C7377

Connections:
24V_F: F1.2, Q90.2 (D)
24V_JACK: F1.1, J1.1
+5V: C3.1, L1.2, U1.1 (FB); also elsewhere on the board
+12V: C5.1, U2.1 (OUT); also elsewhere on the board
+24V: C1.1, C4.1, C6.1, D1.1 (K), D90.1 (A1), Q90.3 (S), R2.1, U1.2 (EN), U1.3 (IN), U2.3 (IN); also elsewhere on the board
BUCK_BST: C2.2, U1.6 (BST)
BUCK_SW: C2.1, L1.1, U1.5 (SW)
GND: C1.2, C3.2, C4.2, C5.2, C6.2, D90.2 (A2), J1.2, R1.2, R3.2, U1.4 (GND), U2.2 (GND); also elsewhere on the board
RPP_G: D1.2 (A), Q90.1 (G), R1.1
V24_DIV: R2.2, R3.1, U3.5 (+)
V24_SENSE: U3.6 (-), U3.7; also elsewhere on the board

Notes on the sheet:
24V input, protection, 5V buck, 12V rail
